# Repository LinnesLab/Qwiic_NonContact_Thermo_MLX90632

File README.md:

SparkFun Melexis MLX90632 Qwiic Breakout
===========================================================

[*SparkX Infrared Non-contact Thermometer (Qwiic) - MLX90632 (SPX-14569)*](https://www.sparkfun.com/products/14569)

The SparkFun Infrared Non-contact Thermometer uses the MLX90632 FIR sensor to detect surface temperature without touching the object. This gives you amazing 1 C prescision from a distance of a few inches.

The [Qwiic system](http://www.sparkfun.com/qwiic) enables fast and solderless connection between popular platforms and various sensors and actuators. You can read more about the Qwiic system [here](http://www.sparkfun.com/qwiic). 

License Information
-------------------

This product is _**open source**_!

Please review the LICENSE.md file for license information.

If you have any questions or concerns on licensing, please contact techsupport@sparkfun.com.

Distributed as-is; no warranty is given.

- Your friends at SparkFun.

_<COLLABORATION CREDIT>_

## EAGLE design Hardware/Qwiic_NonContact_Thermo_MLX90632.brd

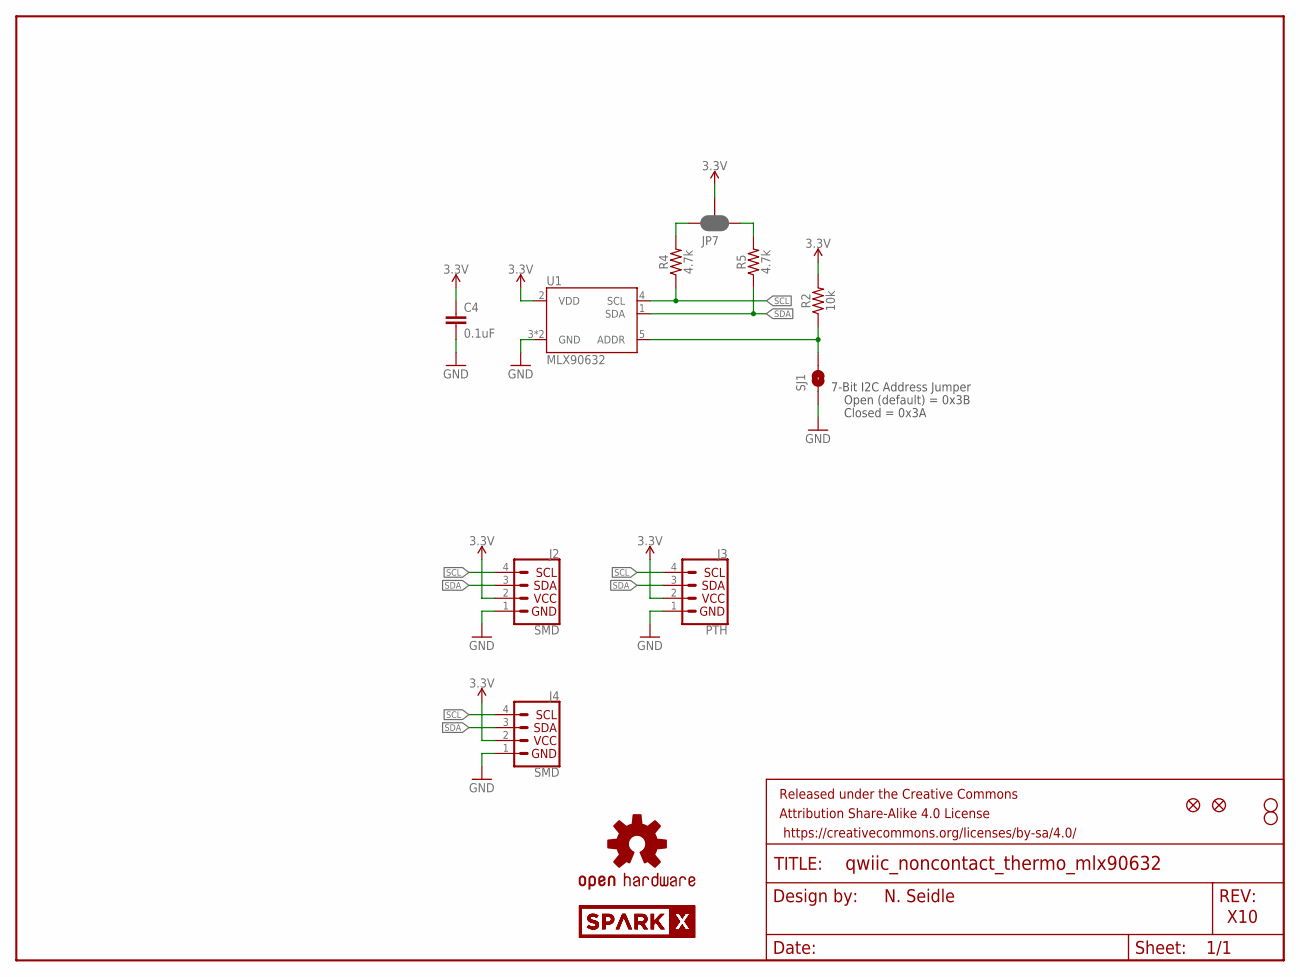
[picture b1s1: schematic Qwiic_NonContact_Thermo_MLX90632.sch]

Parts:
C4: 0.1uF; 0603
FRAME1: FRAME-LETTER; CREATIVE_COMMONS
J2, J4: SMD; 1X04_1MM_RA
J3: PTH; 1X04_NO_SILK
JP2, JP6: FIDUCIALUFIDUCIAL; MICRO-FIDUCIAL
JP3, JP4: STAND-OFF
JP7: JUMPER-SMT_3_2-NC_PASTE_SILK; SMT-JUMPER_3_2-NC_PASTE_SILK
LOGO1: OSHW-LOGOMINI; OSHW-LOGO-MINI
R2: 10k; 0603
R4, R5: 4.7k; 0603
SJ1: SOLDERJUMPERNO; SJ_2S-NO
U1: MLX90632; MLX90632-3X3
U$1, U$2: SPARKX-LOGO4; SPARKX-MEDIUM

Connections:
3.3V: C4.1, J2.2 (VCC), J3.2 (VCC), J4.2 (VCC), JP7.2, R2.2, U1.2 (VDD)
ADDR: R2.1, SJ1.2, U1.5 (ADDR)
GND: C4.2, J2.1 (GND), J3.1 (GND), J4.1 (GND), SJ1.1, U1.3 (GND), U1.6 (GND)
unnamed: JP7.1, R5.2
unnamed: JP7.3, R4.2
SCL: J2.4 (SCL), J3.4 (SCL), J4.4 (SCL), R4.1, U1.4 (SCL)
SDA: J2.3 (SDA), J3.3 (SDA), J4.3 (SDA), R5.1, U1.1 (SDA)

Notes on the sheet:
7-Bit I2C Address Jumper
Closed = 0x3A
Open (default) = 0x3B
N. Seidle
X10

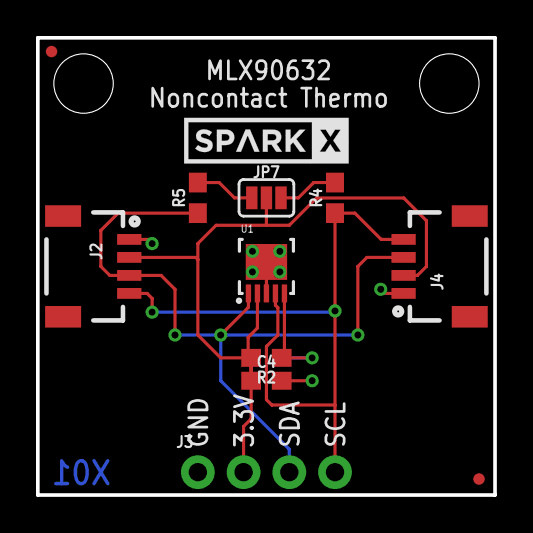
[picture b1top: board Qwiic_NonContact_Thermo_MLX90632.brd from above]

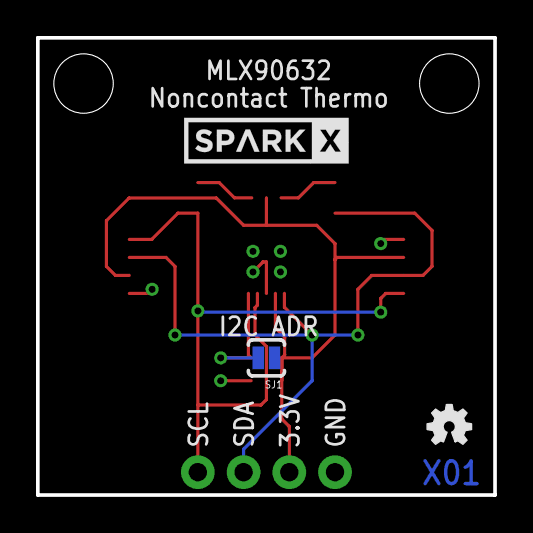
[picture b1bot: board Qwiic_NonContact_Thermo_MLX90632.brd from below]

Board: 2 copper layers, 25.4 x 25.4 mm, 18 parts (3 on the bottom side), 7 nets.

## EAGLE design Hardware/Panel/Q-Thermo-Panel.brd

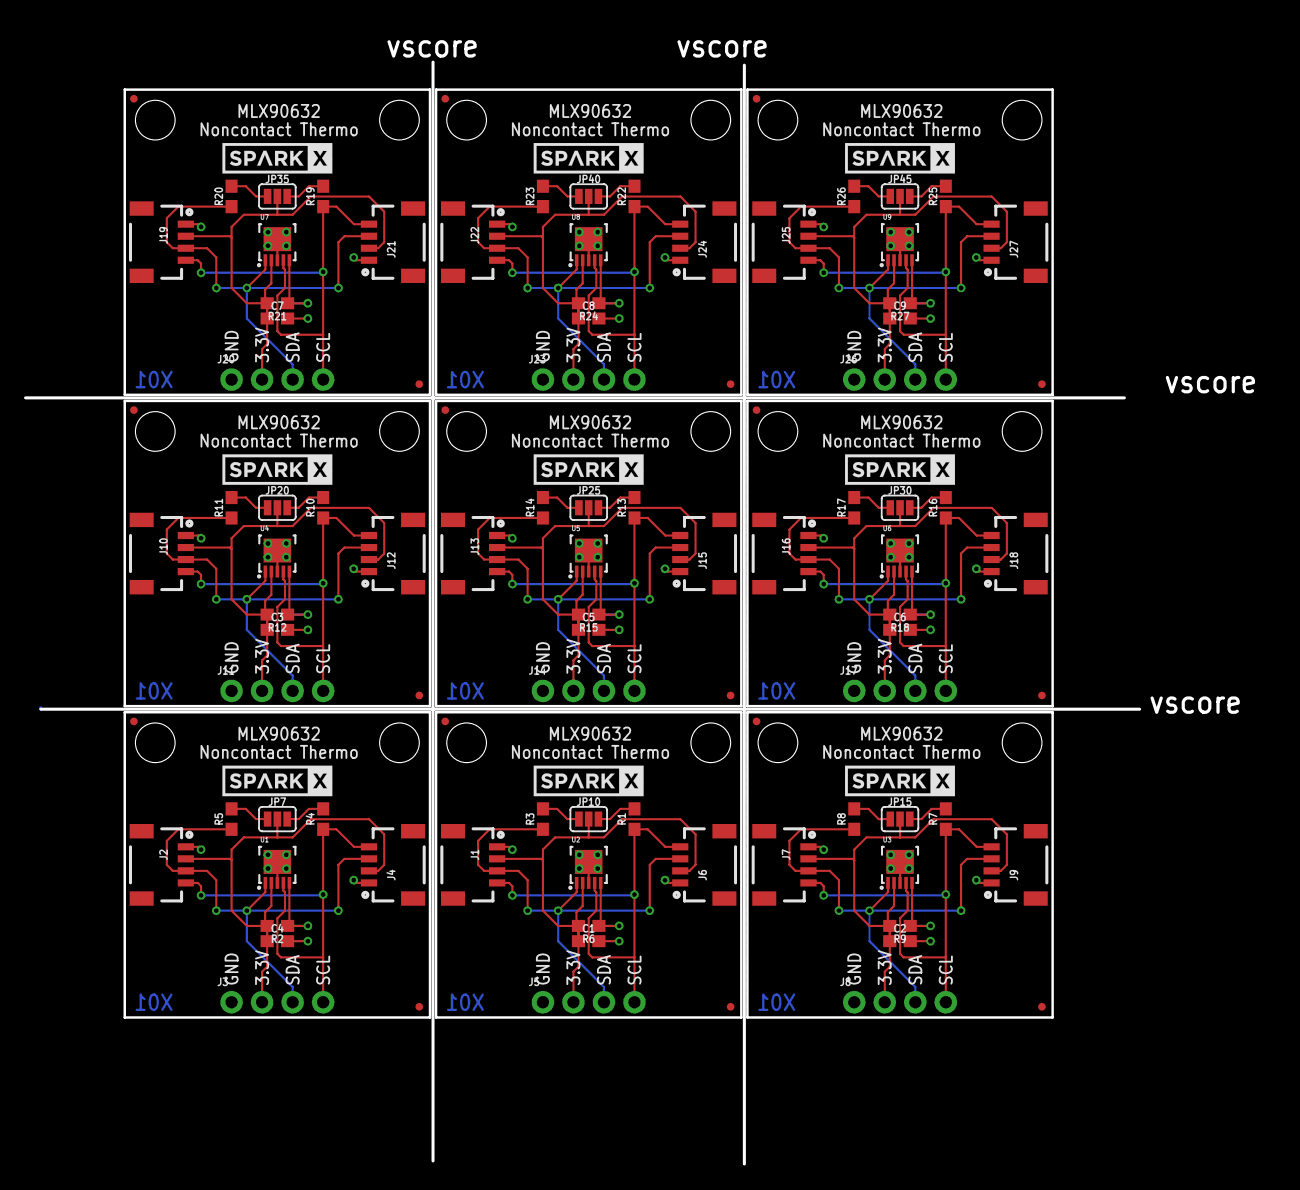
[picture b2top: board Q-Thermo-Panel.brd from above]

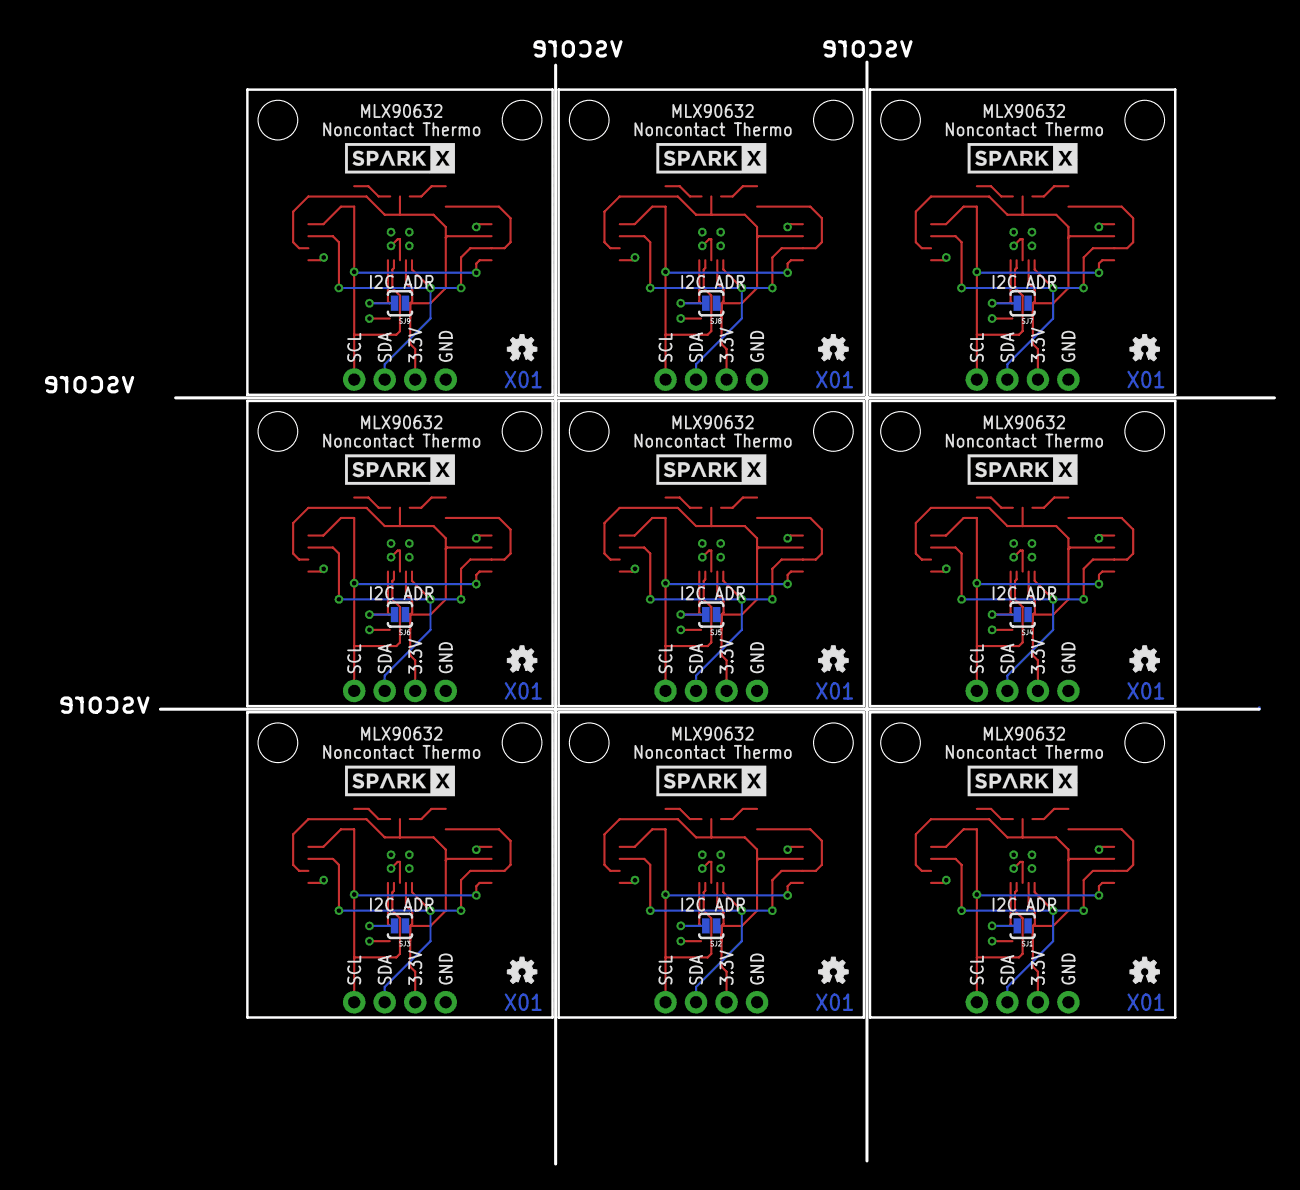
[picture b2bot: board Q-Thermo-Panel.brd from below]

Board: 2 copper layers, 103.9 x 94.7 mm, 153 parts (27 on the bottom side), 63 nets.

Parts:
C1, C2, C3, C4, C5, C6, C7, C8, C9: 0.1uF; 0603
J1, J2, J4, J6, J7, J9, J10, J12, J13, J15, J16, J18, J19, J21, J22, J24, J25, J27: SMD; 1X04_1MM_RA
J3, J5, J8, J11, J14, J17, J20, J23, J26: PTH; 1X04_NO_SILK
JP1, JP3, JP4, JP5, JP11, JP12, JP16, JP17, JP21, JP22, JP26, JP27, JP31, JP32, JP36, JP37, JP41, JP42: STAND-OFF
JP2, JP6, JP8, JP9, JP13, JP14, JP18, JP19, JP23, JP24, JP28, JP29, JP33, JP34, JP38, JP39, JP43, JP44: FIDUCIALUFIDUCIAL; MICRO-FIDUCIAL
JP7, JP10, JP15, JP20, JP25, JP30, JP35, JP40, JP45: SMT-JUMPER_3_2-NC_PASTE_SILK
LOGO1, LOGO2, LOGO3, LOGO4, LOGO5, LOGO6, LOGO7, LOGO8, LOGO9: OSHW-LOGOMINI; OSHW-LOGO-MINI
R1, R3, R4, R5, R7, R8, R10, R11, R13, R14, R16, R17, R19, R20, R22, R23, R25, R26: 4.7k; 0603
R2, R6, R9, R12, R15, R18, R21, R24, R27: 10k; 0603
SJ1, SJ2, SJ3, SJ4, SJ5, SJ6, SJ7, SJ8, SJ9: SJ_2S-NO
U1, U2, U3, U4, U5, U6, U7, U8, U9: MLX90632; MLX90632-3X3
U$1, U$2, U$3, U$4, U$5, U$6, U$7, U$8, U$9, U$10, U$11, U$12, U$13, U$14, U$15, U$16, U$17, U$18: SPARKX-LOGO4; SPARKX-MEDIUM

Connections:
3.3V: C4.1, J2.2, J3.2, J4.2, JP7.2, R2.2, U1.2
3.3V1: C1.1, J1.2, J5.2, J6.2, JP10.2, R6.2, U2.2
3.3V2: C2.1, J7.2, J8.2, J9.2, JP15.2, R9.2, U3.2
3.3V3: C3.1, J10.2, J11.2, J12.2, JP20.2, R12.2, U4.2
3.3V4: C5.1, J13.2, J14.2, J15.2, JP25.2, R15.2, U5.2
3.3V5: C6.1, J16.2, J17.2, J18.2, JP30.2, R18.2, U6.2
3.3V6: C7.1, J19.2, J20.2, J21.2, JP35.2, R21.2, U7.2
3.3V7: C8.1, J22.2, J23.2, J24.2, JP40.2, R24.2, U8.2
3.3V8: C9.1, J25.2, J26.2, J27.2, JP45.2, R27.2, U9.2
ADDR: R2.1, SJ1.2, U1.5
ADDR1: R6.1, SJ2.2, U2.5
ADDR2: R9.1, SJ3.2, U3.5
ADDR3: R12.1, SJ4.2, U4.5
ADDR4: R15.1, SJ5.2, U5.5
ADDR5: R18.1, SJ6.2, U6.5
ADDR6: R21.1, SJ7.2, U7.5
ADDR7: R24.1, SJ8.2, U8.5
ADDR8: R27.1, SJ9.2, U9.5
GND: C4.2, J2.1, J3.1, J4.1, SJ1.1, U1.3, U1.6
GND1: C1.2, J1.1, J5.1, J6.1, SJ2.1, U2.3, U2.6
GND2: C2.2, J7.1, J8.1, J9.1, SJ3.1, U3.3, U3.6
GND3: C3.2, J10.1, J11.1, J12.1, SJ4.1, U4.3, U4.6
GND4: C5.2, J13.1, J14.1, J15.1, SJ5.1, U5.3, U5.6
GND5: C6.2, J16.1, J17.1, J18.1, SJ6.1, U6.3, U6.6
GND6: C7.2, J19.1, J20.1, J21.1, SJ7.1, U7.3, U7.6
GND7: C8.2, J22.1, J23.1, J24.1, SJ8.1, U8.3, U8.6
GND8: C9.2, J25.1, J26.1, J27.1, SJ9.1, U9.3, U9.6
unnamed: JP7.1, R5.2
unnamed: JP7.3, R4.2
unnamed: JP10.1, R3.2
unnamed: JP10.3, R1.2
unnamed: JP15.1, R8.2
unnamed: JP15.3, R7.2
unnamed: JP20.1, R11.2
unnamed: JP20.3, R10.2
unnamed: JP25.1, R14.2
unnamed: JP25.3, R13.2
unnamed: JP30.1, R17.2
unnamed: JP30.3, R16.2
unnamed: JP35.1, R20.2
unnamed: JP35.3, R19.2
unnamed: JP40.1, R23.2
unnamed: JP40.3, R22.2
unnamed: JP45.1, R26.2
unnamed: JP45.3, R25.2
SCL: J2.4, J3.4, J4.4, R4.1, U1.4
SCL1: J1.4, J5.4, J6.4, R1.1, U2.4
SCL2: J7.4, J8.4, J9.4, R7.1, U3.4
SCL3: J10.4, J11.4, J12.4, R10.1, U4.4
SCL4: J13.4, J14.4, J15.4, R13.1, U5.4
SCL5: J16.4, J17.4, J18.4, R16.1, U6.4
SCL6: J19.4, J20.4, J21.4, R19.1, U7.4
SCL7: J22.4, J23.4, J24.4, R22.1, U8.4
SCL8: J25.4, J26.4, J27.4, R25.1, U9.4
SDA: J2.3, J3.3, J4.3, R5.1, U1.1
SDA1: J1.3, J5.3, J6.3, R3.1, U2.1
SDA2: J7.3, J8.3, J9.3, R8.1, U3.1
SDA3: J10.3, J11.3, J12.3, R11.1, U4.1
SDA4: J13.3, J14.3, J15.3, R14.1, U5.1
SDA5: J16.3, J17.3, J18.3, R17.1, U6.1
SDA6: J19.3, J20.3, J21.3, R20.1, U7.1
SDA7: J22.3, J23.3, J24.3, R23.1, U8.1
SDA8: J25.3, J26.3, J27.3, R26.1, U9.1

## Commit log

2018-01-09 :neckbeard: Added .gitattributes & .gitignore files
2018-01-09 Updating readmes

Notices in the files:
parts and their libraries:
SparkFun-Resistors: Licensing: Creative Commons ShareAlike 4.0 International - https://creativecommons.org/licenses/by-sa/4.0
SparkFun-Aesthetics: Released under the Creative Commons Attribution Share-Alike 4.0 License
SparkFun-Aesthetics: https://creativecommons.org/licenses/by-sa/4.0
